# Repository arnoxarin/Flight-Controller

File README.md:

# Flight-Controller
stm32h743 flight controller

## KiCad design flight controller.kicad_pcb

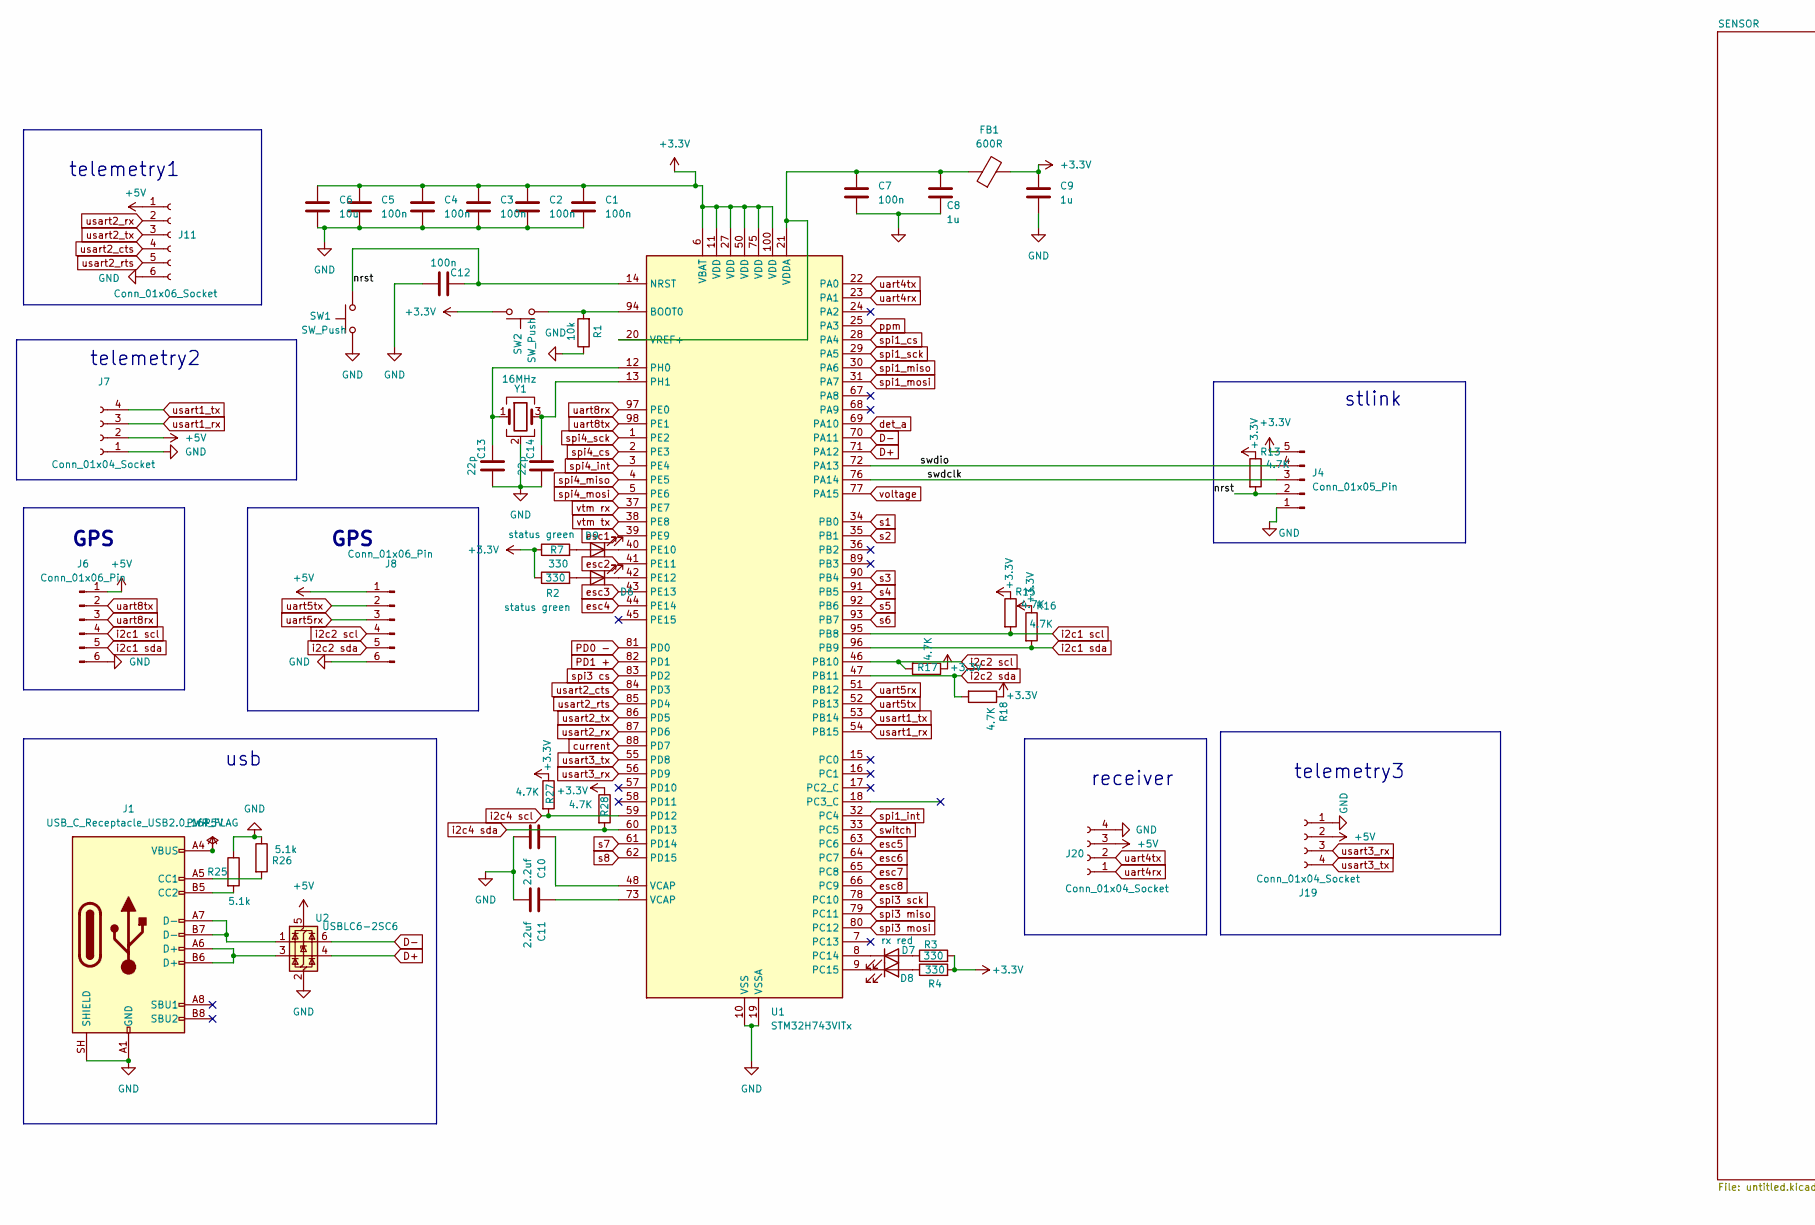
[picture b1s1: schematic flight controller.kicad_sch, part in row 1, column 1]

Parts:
C1, C2, C3, C4, C5, C7, C12: 100n; C_0603_1608Metric
C6: 10u; C_1206_3216Metric
C8, C9: 1u; C_0603_1608Metric
C10, C11: 2.2uf; C_0603_1608Metric
C13, C14: 22p; C_0603_1608Metric
D6, D9: status green; LED_0603_1608Metric
D7: rx red; LED_0603_1608Metric
D8: tx blue; LED_0603_1608Metric
FB1: 600R; L_0805_2012Metric
J1: USB_C_Receptacle_USB2.0_16P; USB_C_Receptacle_GCT_USB4105-xx-A_16P_TopMnt_Horizontal
J4: Conn_01x05_Pin; JST_GH_BM05B-GHS-TBT_1x05-1MP_P1.25mm_Vertical
J6, J8: Conn_01x06_Pin; JST_GH_BM06B-GHS-TBT_1x06-1MP_P1.25mm_Vertical
J7, J19, J20: Conn_01x04_Socket; JST_GH_BM04B-GHS-TBT_1x04-1MP_P1.25mm_Vertical
J11: Conn_01x06_Socket; JST_GH_BM06B-GHS-TBT_1x06-1MP_P1.25mm_Vertical
R1: 10k; R_0603_1608Metric
R2, R3, R4, R7: 330; R_0603_1608Metric
R13, R15, R16, R17, R18, R27, R28: 4.7K; R_0603_1608Metric
R25, R26: 5.1k; R_0603_1608Metric
SW1, SW2: SW_Push; SW_Push_1P1T_NO_CK_KMR2
U1: STM32H743VITx; LQFP-100_14x14mm_P0.5mm
U2: USBLC6-2SC6; SOT-23-6
Y1: 16MHz; Crystal_SMD_3225-4Pin_3.2x2.5mm

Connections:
+3.3V: C1.1, C2.1, C3.1, C4.1, C5.1, C6.1, C9.1, FB1.2, J4.5, R2.1, R3.2, R4.2, R7.1, R13.1, R15.1, R16.1, R17.1, R18.1, R27.1, R28.1, SW2.2, U1.6 (VBAT), U1.11 (VDD), U1.27 (VDD), U1.50 (VDD), U1.75 (VDD), U1.100 (VDD); also elsewhere on the board
+5V: J1.A4 (VBUS), J1.A9 (VBUS), J1.B4 (VBUS), J1.B9 (VBUS), J6.1, J7.2, J8.1, J11.1, J19.2, J20.3, U2.5 (VBUS); also elsewhere on the board
/nrst: C12.2, J4.2, R13.2, SW1.2, U1.14 (NRST)
/swdclk: J4.3, U1.76 (PA14)
/swdio: J4.4, U1.72 (PA13)
D+: U1.71 (PA12), U2.4 (I/O2)
D-: U1.70 (PA11), U2.6 (I/O1)
GND: C1.2, C2.2, C3.2, C4.2, C5.2, C6.2, C7.2, C8.2, C9.2, C10.2, C11.2, C12.1, C13.1, C14.1, J1.A1 (GND), J1.A12 (GND), J1.B1 (GND), J1.B12 (GND), J1.SH (SHIELD), J4.1, J6.6, J7.1, J8.6, J11.6, J19.1, J20.4, R1.1, R25.1, R26.1, SW1.1, U1.10 (VSS), U1.19 (VSSA), U1.26 (VSS), U1.49 (VSS), U1.74 (VSS), U1.99 (VSS), U2.2 (GND), Y1.2 (G), Y1.4 (G); also elsewhere on the board
unnamed: C10.1, U1.48 (VCAP)
unnamed: C11.1, U1.73 (VCAP)
unnamed: D6.2 (A), R2.2
unnamed: D6.1 (K), U1.42 (PE12)
unnamed: D7.2 (A), R3.1
unnamed: D7.1 (K), U1.8 (PC14)
unnamed: D8.2 (A), R4.1
unnamed: D8.1 (K), U1.9 (PC15)
unnamed: D9.2 (A), R7.2
unnamed: D9.1 (K), U1.40 (PE10)
unnamed: J1.A5 (CC1), R26.2
unnamed: J1.B5 (CC2), R25.2
unnamed: J1.A6 (D+), J1.B6 (D+), U2.3 (I/O2)
unnamed: J1.A7 (D-), J1.B7 (D-), U2.1 (I/O1)
unnamed: R1.2, SW2.1, U1.94 (BOOT0)
unnamed: C13.2, U1.12 (PH0), Y1.1
unnamed: C14.2, U1.13 (PH1), Y1.3
unnamed: C7.1, C8.1, FB1.1, U1.20 (VREF+), U1.21 (VDDA)
PD0 -: U1.81 (PD0); also elsewhere on the board
PD1 +: U1.82 (PD1); also elsewhere on the board
current: U1.88 (PD7); also elsewhere on the board
det_a: U1.69 (PA10); also elsewhere on the board
esc1: U1.39 (PE9); also elsewhere on the board
esc2: U1.41 (PE11); also elsewhere on the board
esc3: U1.43 (PE13); also elsewhere on the board
esc4: U1.44 (PE14); also elsewhere on the board
esc5: U1.63 (PC6); also elsewhere on the board
esc6: U1.64 (PC7); also elsewhere on the board
esc7: U1.65 (PC8); also elsewhere on the board
esc8: U1.66 (PC9); also elsewhere on the board
i2c1 scl: J6.4, R15.2, U1.95 (PB8)
i2c1 sda: J6.5, R16.2, U1.96 (PB9)
i2c2 scl: J8.4, R17.2, U1.46 (PB10)
i2c2 sda: J8.5, R18.2, U1.47 (PB11)
i2c4 scl: R27.2, U1.59 (PD12); also elsewhere on the board
i2c4 sda: R28.2, U1.60 (PD13); also elsewhere on the board
ppm: U1.25 (PA3); also elsewhere on the board
s1: U1.34 (PB0); also elsewhere on the board
s2: U1.35 (PB1); also elsewhere on the board
s3: U1.90 (PB4); also elsewhere on the board
s4: U1.91 (PB5); also elsewhere on the board
s5: U1.92 (PB6); also elsewhere on the board
s6: U1.93 (PB7); also elsewhere on the board
s7: U1.61 (PD14); also elsewhere on the board
s8: U1.62 (PD15); also elsewhere on the board
spi1_cs: U1.28 (PA4); also elsewhere on the board
spi1_int: U1.32 (PC4); also elsewhere on the board
spi1_miso: U1.30 (PA6); also elsewhere on the board
spi1_mosi: U1.31 (PA7); also elsewhere on the board
spi1_sck: U1.29 (PA5); also elsewhere on the board
spi3 cs: U1.83 (PD2); also elsewhere on the board
spi3 miso: U1.79 (PC11); also elsewhere on the board
spi3 mosi: U1.80 (PC12); also elsewhere on the board
spi3 sck: U1.78 (PC10); also elsewhere on the board
spi4_cs: U1.2 (PE3); also elsewhere on the board
spi4_int: U1.3 (PE4); also elsewhere on the board
spi4_miso: U1.4 (PE5); also elsewhere on the board
spi4_mosi: U1.5 (PE6); also elsewhere on the board
spi4_sck: U1.1 (PE2); also elsewhere on the board
switch: U1.33 (PC5); also elsewhere on the board
uart4rx: J20.1, U1.23 (PA1)
uart4tx: J20.2, U1.22 (PA0)
uart5rx: J8.3, U1.51 (PB12)
uart5tx: J8.2, U1.52 (PB13)
uart8rx: J6.3, U1.97 (PE0)
uart8tx: J6.2, U1.98 (PE1)
usart1_rx: J7.3, U1.54 (PB15)
usart1_tx: J7.4, U1.53 (PB14)
usart2_cts: J11.4, U1.84 (PD3)
usart2_rts: J11.5, U1.85 (PD4)
usart2_rx: J11.2, U1.87 (PD6)
usart2_tx: J11.3, U1.86 (PD5)
usart3_rx: J19.3, U1.56 (PD9)
usart3_tx: J19.4, U1.55 (PD8)
voltage: U1.77 (PA15); also elsewhere on the board
vtm rx: U1.37 (PE7); also elsewhere on the board
vtm tx: U1.38 (PE8); also elsewhere on the board

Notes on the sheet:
receiver
usb
telemetry2
GPS
telemetry1
stlink
telemetry3

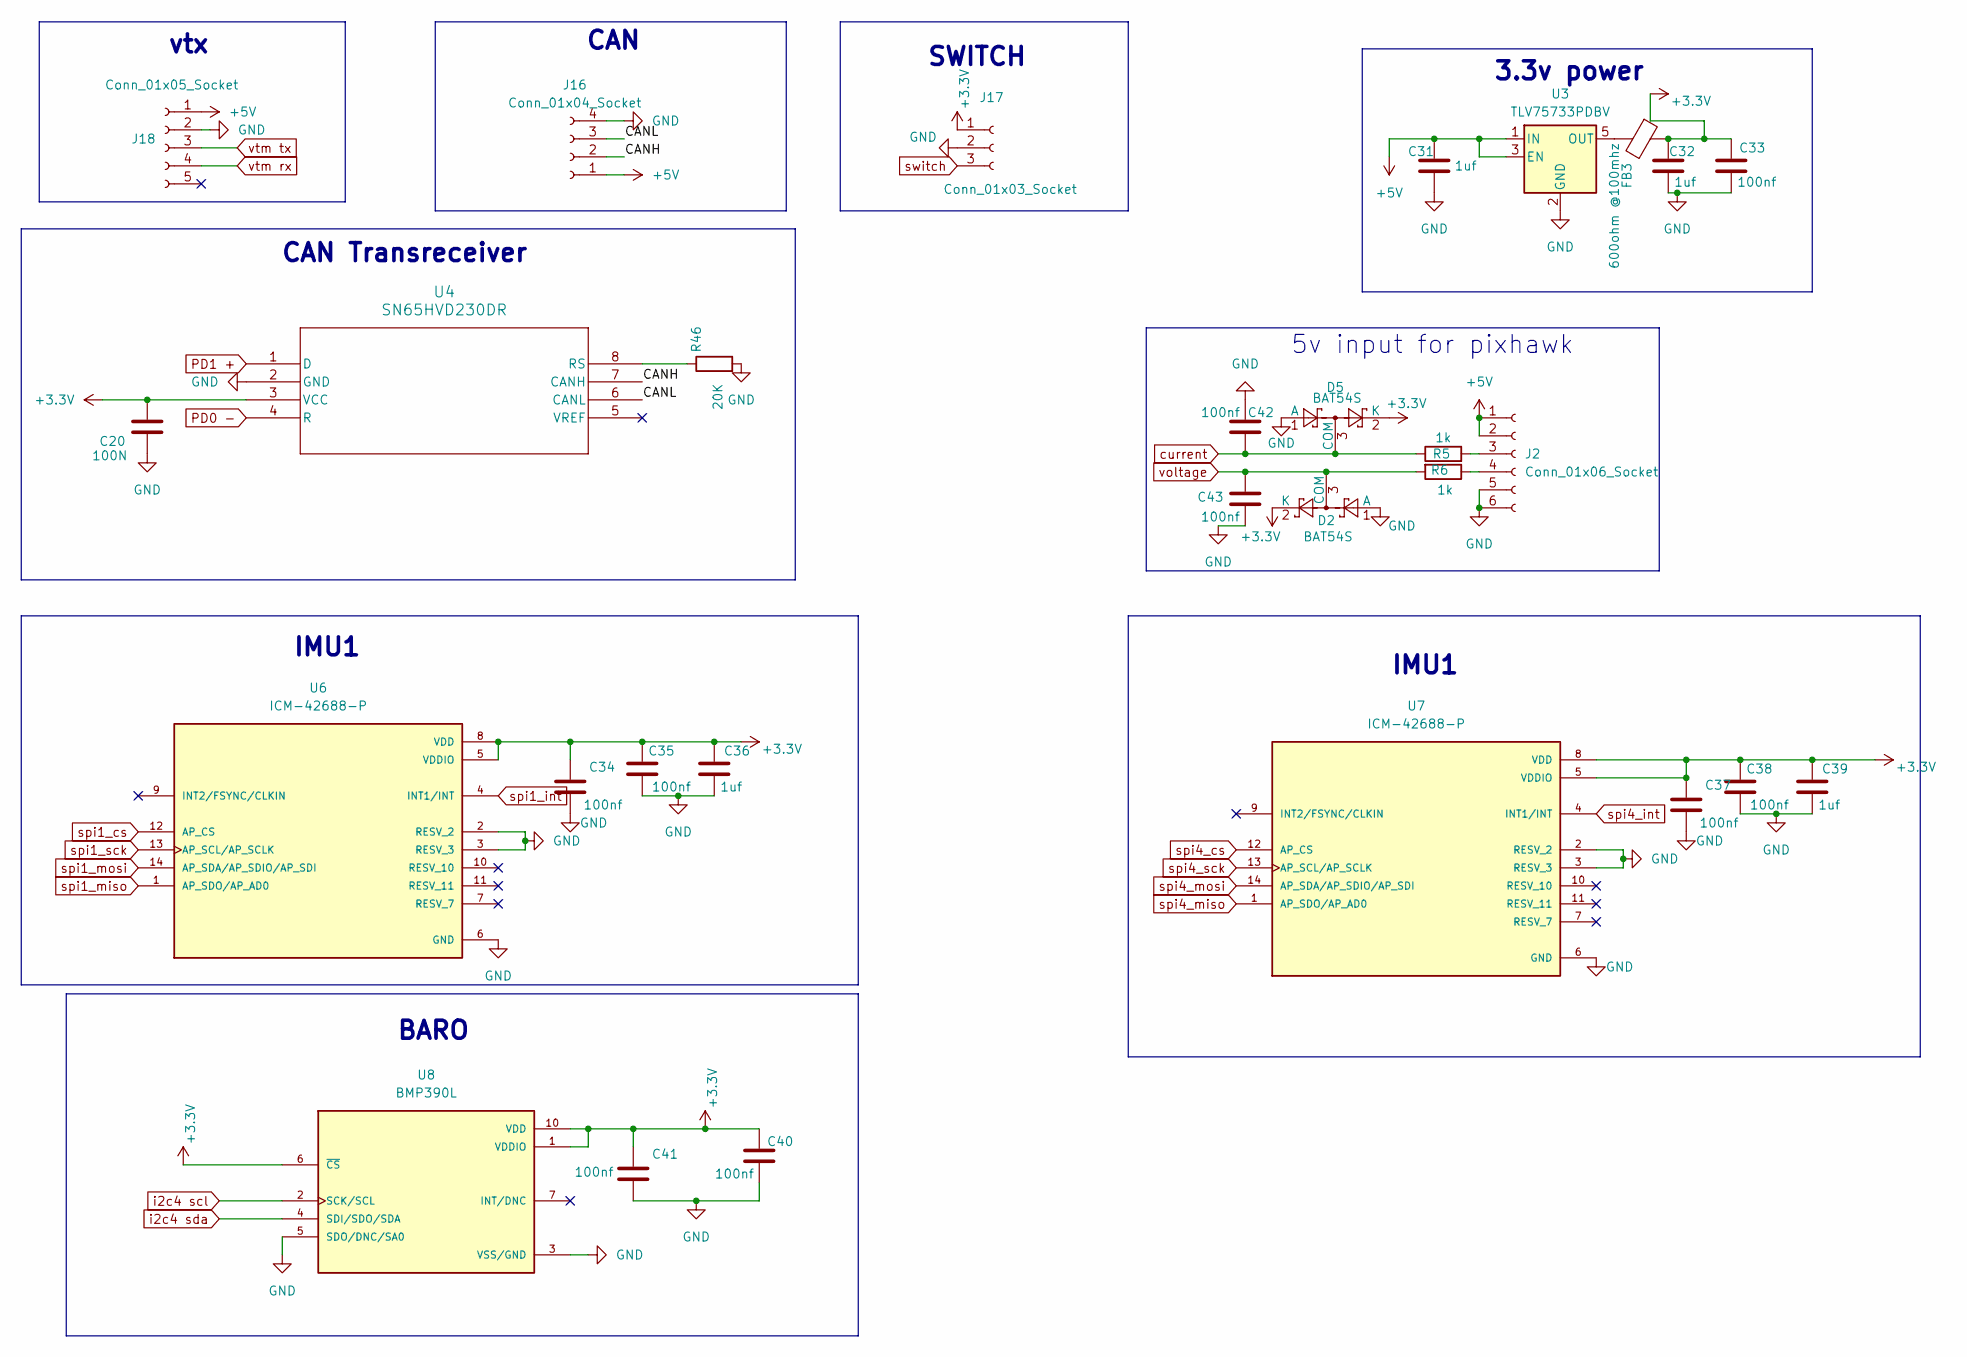
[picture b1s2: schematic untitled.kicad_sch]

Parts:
C20: 100N; C_0603_1608Metric
C31, C32, C36, C39: 1uf; C_0603_1608Metric
C33, C34, C35, C37, C38, C40, C41, C42, C43: 100nf; C_0603_1608Metric
D2, D5: BAT54S; SOT-23
FB3: 600ohm @100mhz; L_0805_2012Metric
J2: Conn_01x06_Socket; JST_GH_BM06B-GHS-TBT_1x06-1MP_P1.25mm_Vertical
J16: Conn_01x04_Socket; JST_GH_BM04B-GHS-TBT_1x04-1MP_P1.25mm_Vertical
J17: Conn_01x03_Socket; JST_GH_BM03B-GHS-TBT_1x03-1MP_P1.25mm_Vertical
J18: Conn_01x05_Socket; JST_GH_BM05B-GHS-TBT_1x05-1MP_P1.25mm_Vertical
R5, R6: 1k; R_0603_1608Metric
R46: 20K; R_0603_1608Metric
U3: TLV75733PDBV; SC-74A-5_1.55x2.9mm_P0.95mm
U4: SN65HVD230DR; D8
U6, U7: ICM-42688-P; LGA-14_3x2.5mm_P0.5mm_LayoutBorder3x4y; PARTREV 1.2
U8: BMP390L; XDCR_BMP390L; PARTREV 1.7

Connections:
+3.3V: C20.1, C32.1, C33.1, C34.1, C35.1, C36.1, C37.1, C38.1, C39.1, C40.1, C41.1, D2.2 (K), D5.2 (K), FB3.1, J17.1, U4.3 (VCC), U6.5 (VDDIO), U6.8 (VDD), U7.5 (VDDIO), U7.8 (VDD), U8.1 (VDDIO), U8.6 (~CS), U8.10 (VDD); also elsewhere on the board
+5V: C31.1, J2.1, J2.2, J16.1, J18.1, U3.1 (IN), U3.3 (EN); also elsewhere on the board
/SENSOR/CANH: J16.2, U4.7 (CANH)
/SENSOR/CANL: J16.3, U4.6 (CANL)
GND: C20.2, C31.2, C32.2, C33.2, C34.2, C35.2, C36.2, C37.2, C38.2, C39.2, C40.2, C41.2, C42.1, C43.2, D2.1 (A), D5.1 (A), J2.5, J2.6, J16.4, J17.2, J18.2, R46.2, U3.2 (GND), U4.2 (GND), U6.2 (RESV_2), U6.3 (RESV_3), U6.6 (GND), U7.2 (RESV_2), U7.3 (RESV_3), U7.6 (GND), U8.3 (VSS/GND), U8.5 (SDO/DNC/SA0), U8.8 (VSS/GND), U8.9 (VSS/GND); also elsewhere on the board
unnamed: J2.3, R5.2
unnamed: J2.4, R6.1
unnamed: FB3.2, U3.5 (OUT)
unnamed: R46.1, U4.8 (RS)
PD0 -: U4.4 (R); also elsewhere on the board
PD1 +: U4.1 (D); also elsewhere on the board
current: C42.2, D5.3 (COM), R5.1; also elsewhere on the board
i2c4 scl: U8.2 (SCK/SCL); also elsewhere on the board
i2c4 sda: U8.4 (SDI/SDO/SDA); also elsewhere on the board
spi1_cs: U6.12 (AP_CS); also elsewhere on the board
spi1_int: U6.4 (INT1/INT); also elsewhere on the board
spi1_miso: U6.1 (AP_SDO/AP_AD0); also elsewhere on the board
spi1_mosi: U6.14 (AP_SDA/AP_SDIO/AP_SDI); also elsewhere on the board
spi1_sck: U6.13 (AP_SCL/AP_SCLK); also elsewhere on the board
spi4_cs: U7.12 (AP_CS); also elsewhere on the board
spi4_int: U7.4 (INT1/INT); also elsewhere on the board
spi4_miso: U7.1 (AP_SDO/AP_AD0); also elsewhere on the board
spi4_mosi: U7.14 (AP_SDA/AP_SDIO/AP_SDI); also elsewhere on the board
spi4_sck: U7.13 (AP_SCL/AP_SCLK); also elsewhere on the board
switch: J17.3; also elsewhere on the board
voltage: C43.1, D2.3 (COM), R6.2; also elsewhere on the board
vtm rx: J18.4; also elsewhere on the board
vtm tx: J18.3; also elsewhere on the board

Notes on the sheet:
BARO
IMU1
SWITCH
5v input for pixhawk
vtx
CAN Transreceiver
CAN
3.3v power

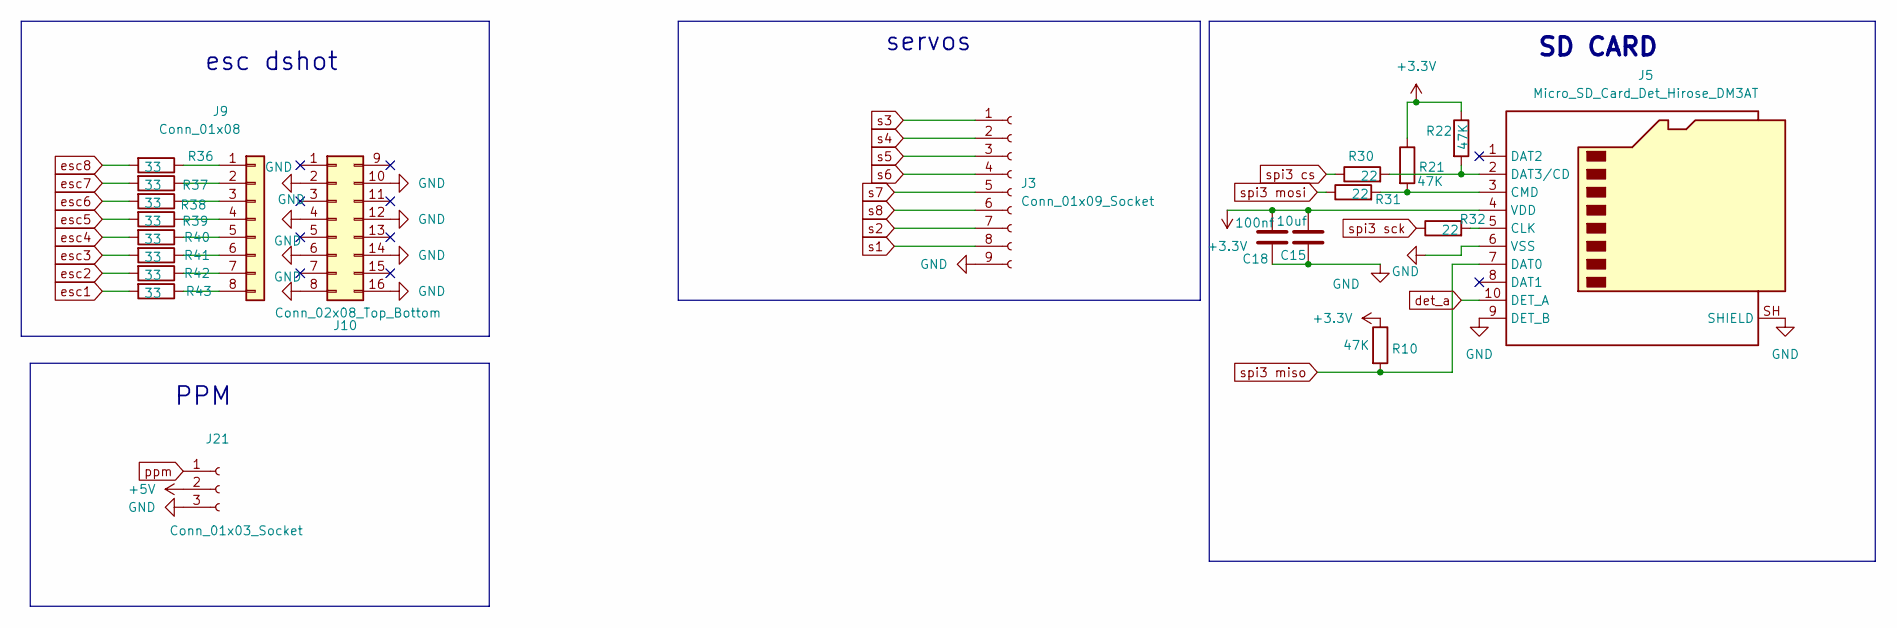
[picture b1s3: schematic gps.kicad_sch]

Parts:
C15: 10uf; C_1206_3216Metric
C18: 100nf; C_0603_1608Metric
J3: Conn_01x09_Socket; JST_GH_BM09B-GHS-TBT_1x09-1MP_P1.25mm_Vertical
J5: Micro_SD_Card_Det_Hirose_DM3AT; microSD_HC_Molex_104031-0811
J9: Conn_01x08; PinHeader_1x08_P2.54mm_Vertical
J10: Conn_02x08_Top_Bottom; PinHeader_2x08_P2.54mm_Vertical
J21: Conn_01x03_Socket; JST_GH_BM03B-GHS-TBT_1x03-1MP_P1.25mm_Vertical
R10, R21, R22: 47K; R_0603_1608Metric
R30, R31, R32: 22; R_0603_1608Metric
R36, R37, R38, R39, R40, R41, R42, R43: 33; R_0603_1608Metric

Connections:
+3.3V: C15.1, C18.1, J5.4 (VDD), R10.1, R21.1, R22.1; also elsewhere on the board
+5V: J21.2; also elsewhere on the board
GND: C15.2, C18.2, J3.9, J5.6 (VSS), J5.9 (DET_B), J5.SH (SHIELD), J10.2, J10.4, J10.6, J10.8, J10.10, J10.12, J10.14, J10.16, J21.3; also elsewhere on the board
unnamed: J5.5 (CLK), R32.2
unnamed: J5.3 (CMD), R21.2, R31.2
unnamed: J5.2 (DAT3/CD), R22.2, R30.2
unnamed: J9.1, R36.1
unnamed: J9.2, R37.1
unnamed: J9.3, R38.1
unnamed: J9.4, R39.1
unnamed: J9.5, R40.1
unnamed: J9.6, R41.1
unnamed: J9.7, R42.1
unnamed: J9.8, R43.1
det_a: J5.10 (DET_A); also elsewhere on the board
esc1: R43.2; also elsewhere on the board
esc2: R42.2; also elsewhere on the board
esc3: R41.2; also elsewhere on the board
esc4: R40.2; also elsewhere on the board
esc5: R39.2; also elsewhere on the board
esc6: R38.2; also elsewhere on the board
esc7: R37.2; also elsewhere on the board
esc8: R36.2; also elsewhere on the board
ppm: J21.1; also elsewhere on the board
s1: J3.8; also elsewhere on the board
s2: J3.7; also elsewhere on the board
s3: J3.1; also elsewhere on the board
s4: J3.2; also elsewhere on the board
s5: J3.3; also elsewhere on the board
s6: J3.4; also elsewhere on the board
s7: J3.5; also elsewhere on the board
s8: J3.6; also elsewhere on the board
spi3 cs: R30.1; also elsewhere on the board
spi3 miso: J5.7 (DAT0), R10.2; also elsewhere on the board
spi3 mosi: R31.1; also elsewhere on the board
spi3 sck: R32.1; also elsewhere on the board

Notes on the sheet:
servos
esc dshot
PPM
SD CARD

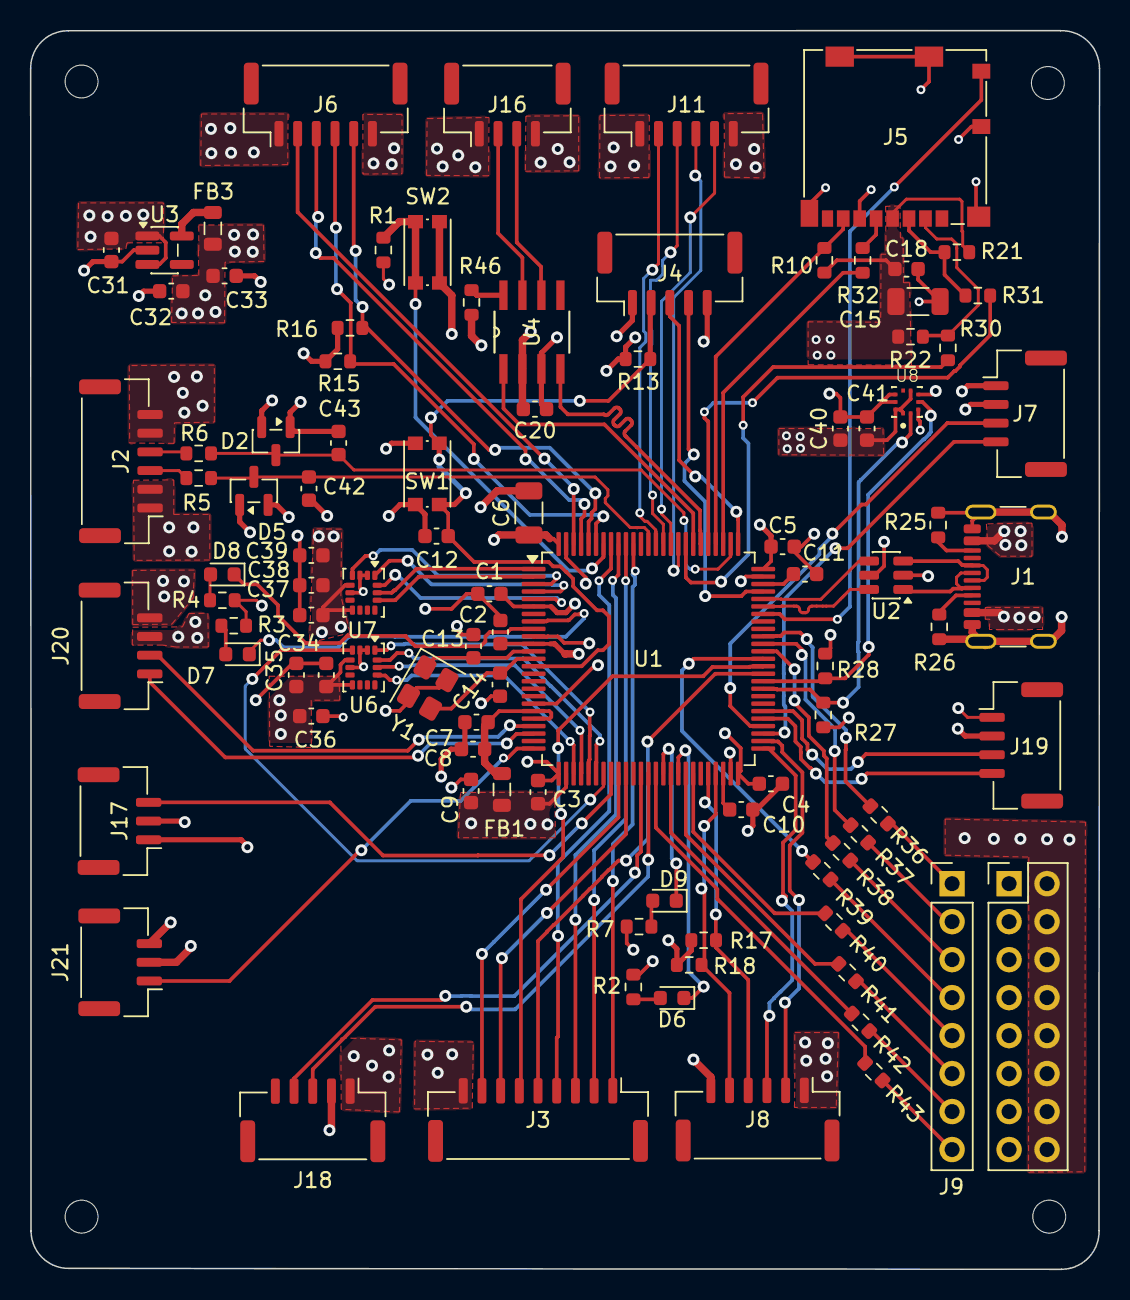
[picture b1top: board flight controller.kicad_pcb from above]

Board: 4 copper layers, 71.5 x 82.8 mm, 96 parts (0 on the bottom side), 102 nets.
